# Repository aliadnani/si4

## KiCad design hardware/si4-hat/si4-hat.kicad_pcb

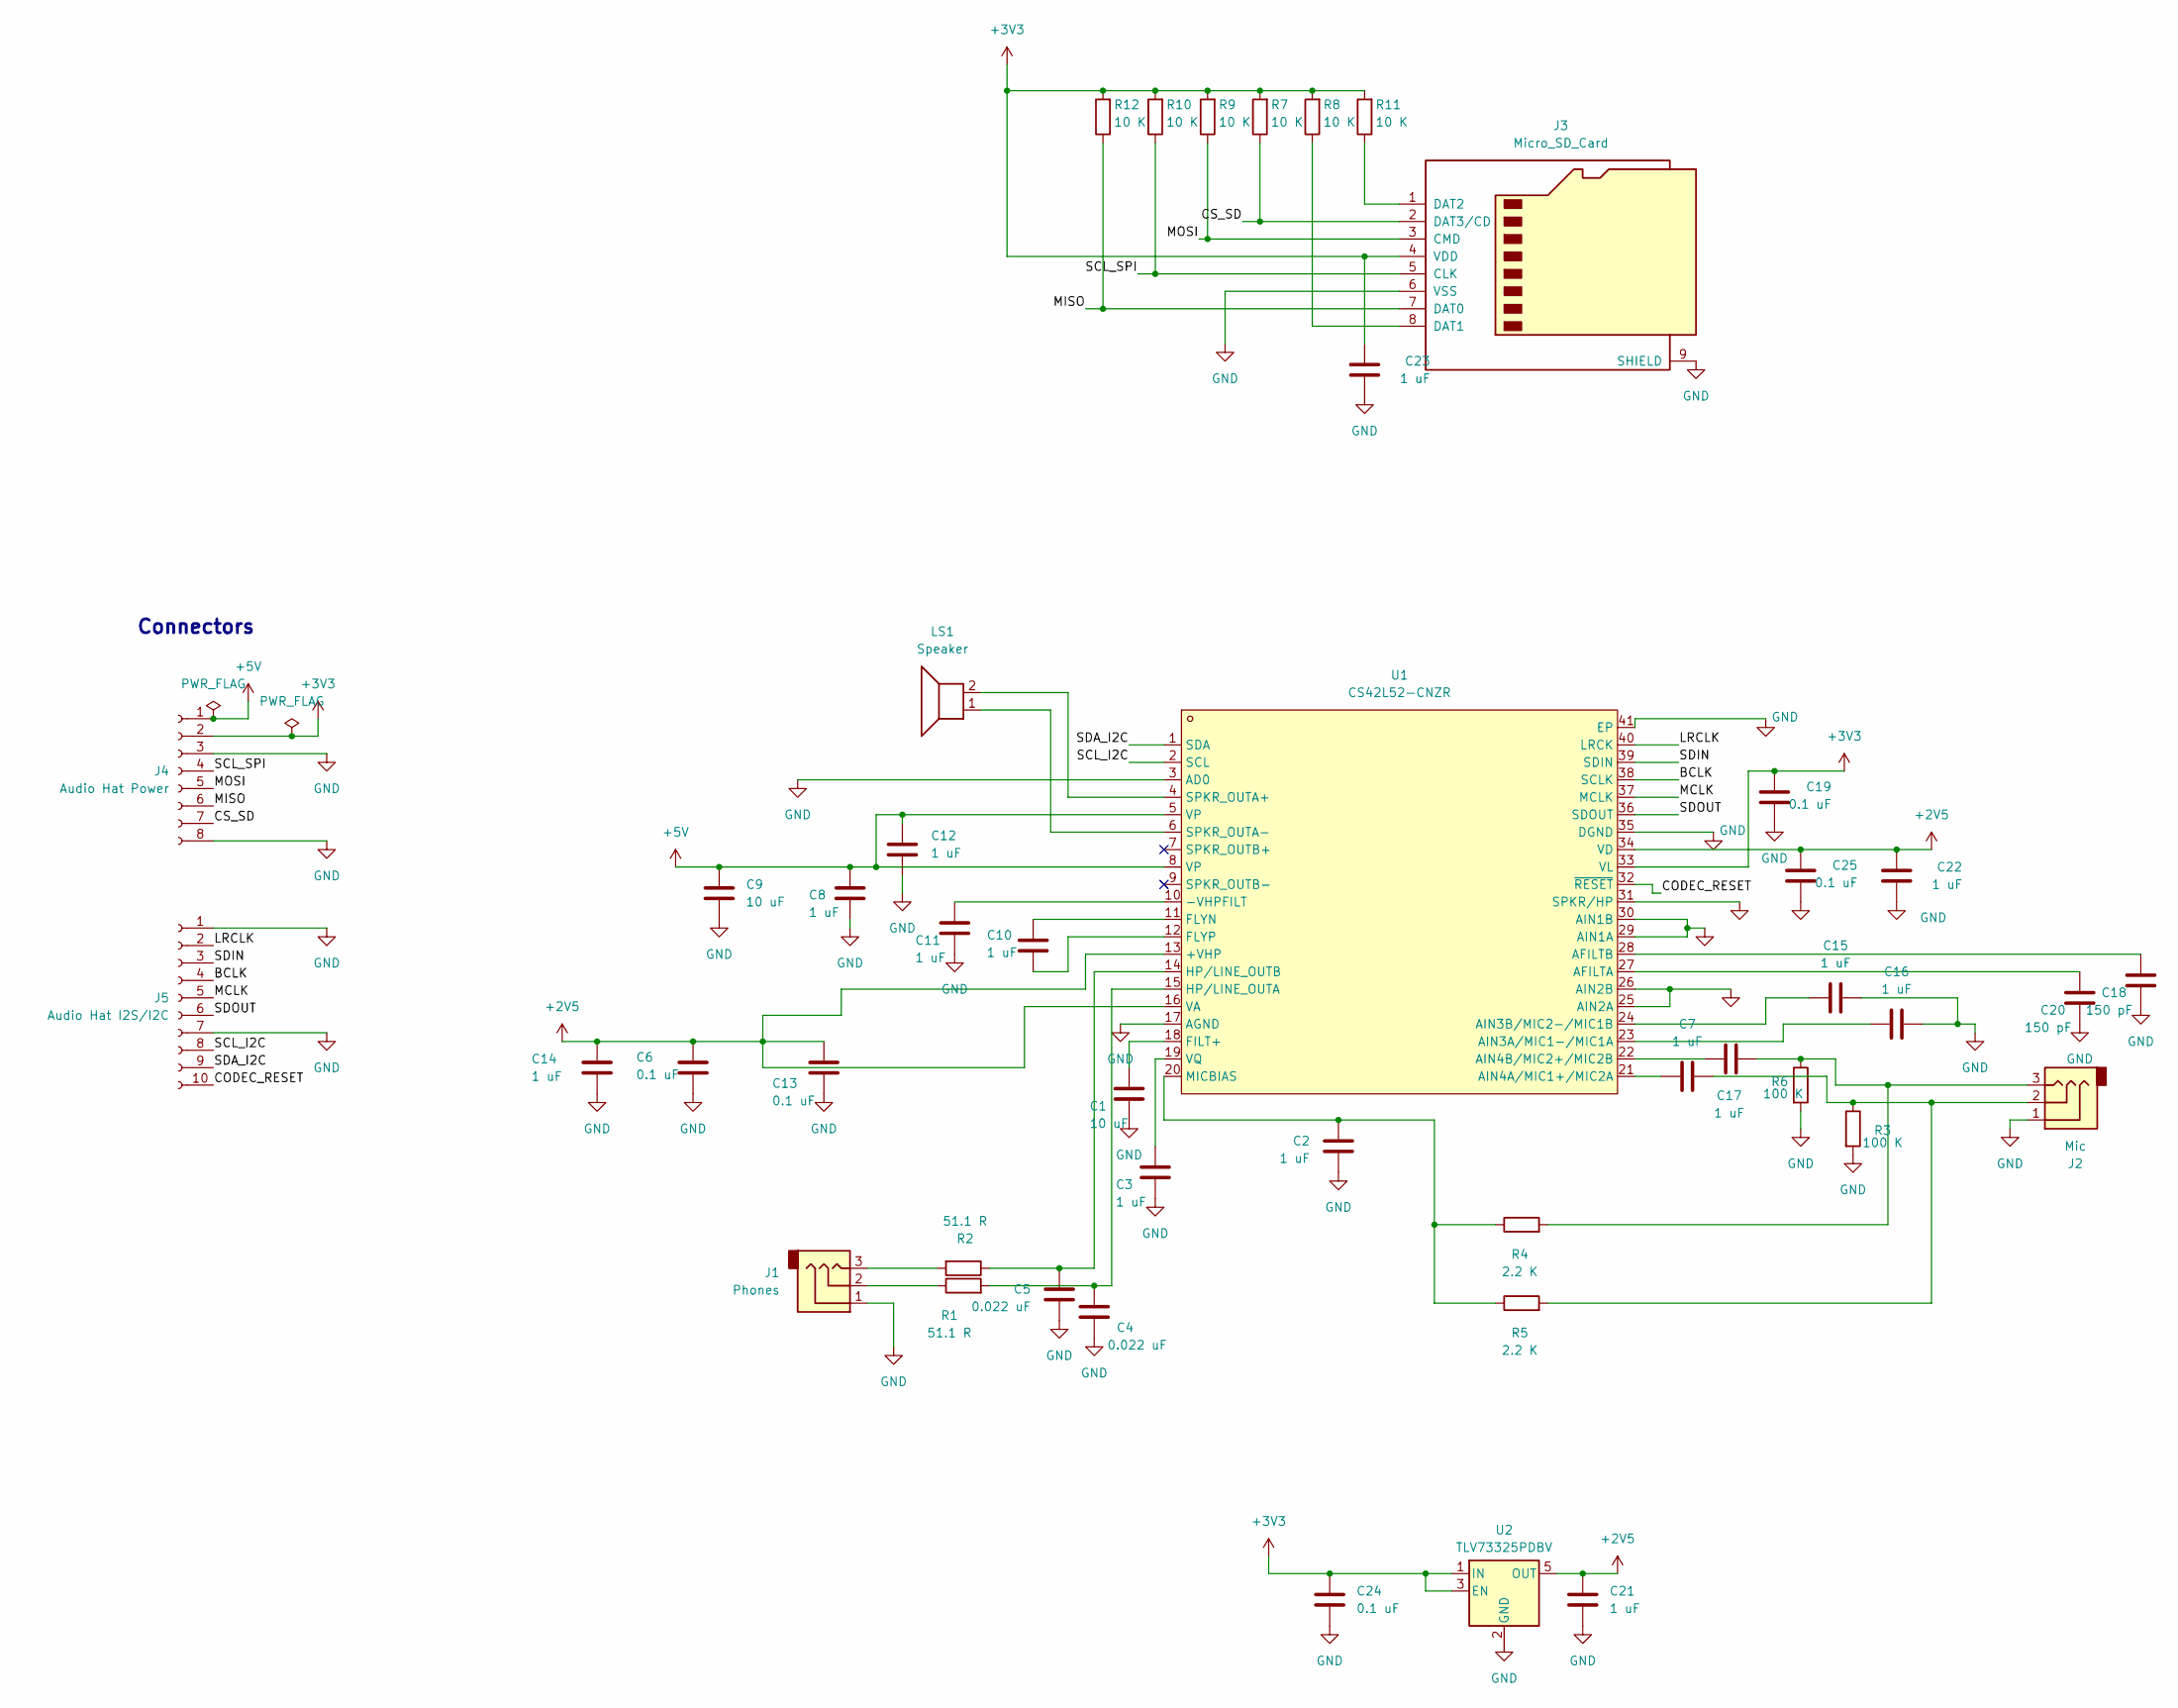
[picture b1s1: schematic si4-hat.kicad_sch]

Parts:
C1, C9: 10 uF; C_0805_2012Metric
C2, C3, C7, C8, C10, C11, C12, C14, C15, C16, C17, C21, C22, C23: 1 uF; C_0805_2012Metric
C4, C5: 0.022 uF; C_0805_2012Metric
C6, C13, C19, C24, C25: 0.1 uF; C_0805_2012Metric
C18, C20: 150 pF; C_0805_2012Metric
J1: Phones; AUDIO-TH_PJ-309A-2; JLC_3DModel_Q b7cd142673524e80947edf82ed32f13f
J2: Mic; AUDIO-TH_PJ-309A-2; JLC_3DModel_Q b7cd142673524e80947edf82ed32f13f
J3: Micro_SD_Card; microSD_HC_Hirose_DM3AT-SF-PEJM5
J4: Audio Hat Power; PinHeader_1x08_P1.27mm_Vertical
J5: Audio Hat I2S/I2C; PinHeader_1x10_P1.27mm_Vertical
LS1: Speaker; SolderWire-0.15sqmm_1x02_P4mm_D0.5mm_OD1.5mm
R1, R2: 51.1 R; R_0805_2012Metric
R3, R6: 100 K; R_0805_2012Metric
R4, R5: 2.2 K; R_0805_2012Metric
R7, R8, R9, R10, R11, R12: 10 K; R_0805_2012Metric
U1: CS42L52-CNZR; QFN-40_L6.0-W6.0-P0.50-TL-EP4.1; LCSC Part C17429034
U2: TLV73325PDBV; SOT-23-5

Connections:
+2V5: C6.1, C13.1, C14.1, C21.1, C22.1, C25.1, U1.13 (+VHP), U1.16 (VA), U1.34 (VD), U2.5 (OUT)
+3V3: C19.1, C23.1, C24.1, J3.4 (VDD), J4.2, R7.2, R8.2, R9.2, R10.2, R11.2, R12.2, U1.33 (VL), U2.1 (IN), U2.3 (EN)
+5V: C8.1, C9.1, C12.1, J4.1, U1.5 (VP), U1.8 (VP)
/BCLK: J5.4, U1.38 (SCLK)
/CODEC_RESET: J5.10, U1.32 (~RESET)
/CS_SD: J3.2 (DAT3/CD), J4.7, R7.1
/LRCLK: J5.2, U1.40 (LRCK)
/MCLK: J5.5, U1.37 (MCLK)
/MISO: J3.7 (DAT0), J4.6, R12.1
/MOSI: J3.3 (CMD), J4.5, R9.1
/SCL_I2C: J5.8, U1.2 (SCL)
/SCL_SPI: J3.5 (CLK), J4.4, R10.1
/SDA_I2C: J5.9, U1.1 (SDA)
/SDIN: J5.3, U1.39 (SDIN)
/SDOUT: J5.6, U1.36 (SDOUT)
GND: C1.2, C2.2, C3.2, C4.2, C5.2, C6.2, C8.2, C9.2, C11.2, C12.2, C13.2, C14.2, C15.1, C16.1, C18.2, C19.2, C20.2, C21.2, C22.2, C23.2, C24.2, C25.2, J1.1, J2.1, J3.6 (VSS), J3.9 (SHIELD), J4.3, J4.8, J5.1, J5.7, R3.2, R6.2, U1.3 (AD0), U1.17 (AGND), U1.25 (AIN2A), U1.26 (AIN2B), U1.29 (AIN1A), U1.30 (AIN1B), U1.31 (SPKR/HP), U1.35 (DGND), U1.41 (EP), U2.2 (GND)
unnamed: C7.1, J2.2, R3.1, R5.2
unnamed: C17.1, J2.3, R4.2, R6.1
unnamed: J1.2, R1.1
unnamed: J1.3, R2.2
unnamed: J3.8 (DAT1), R8.1
unnamed: J3.1 (DAT2), R11.1
unnamed: C11.1, U1.10 (-VHPFILT)
unnamed: C20.1, U1.27 (AFILTA)
unnamed: C18.1, U1.28 (AFILTB)
unnamed: C16.2, U1.23 (AIN3A/MIC1-/MIC1A)
unnamed: C15.2, U1.24 (AIN3B/MIC2-/MIC1B)
unnamed: C7.2, U1.21 (AIN4A/MIC1+/MIC2A)
unnamed: C17.2, U1.22 (AIN4B/MIC2+/MIC2B)
unnamed: C1.1, U1.18 (FILT+)
unnamed: C10.1, U1.11 (FLYN)
unnamed: C10.2, U1.12 (FLYP)
unnamed: C4.1, R1.2, U1.15 (HP/LINE_OUTA)
unnamed: C5.1, R2.1, U1.14 (HP/LINE_OUTB)
unnamed: C2.1, R4.1, R5.1, U1.20 (MICBIAS)
unnamed: LS1.2, U1.4 (SPKR_OUTA+)
unnamed: LS1.1, U1.6 (SPKR_OUTA-)
unnamed: C3.1, U1.19 (VQ)

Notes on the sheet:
Connectors

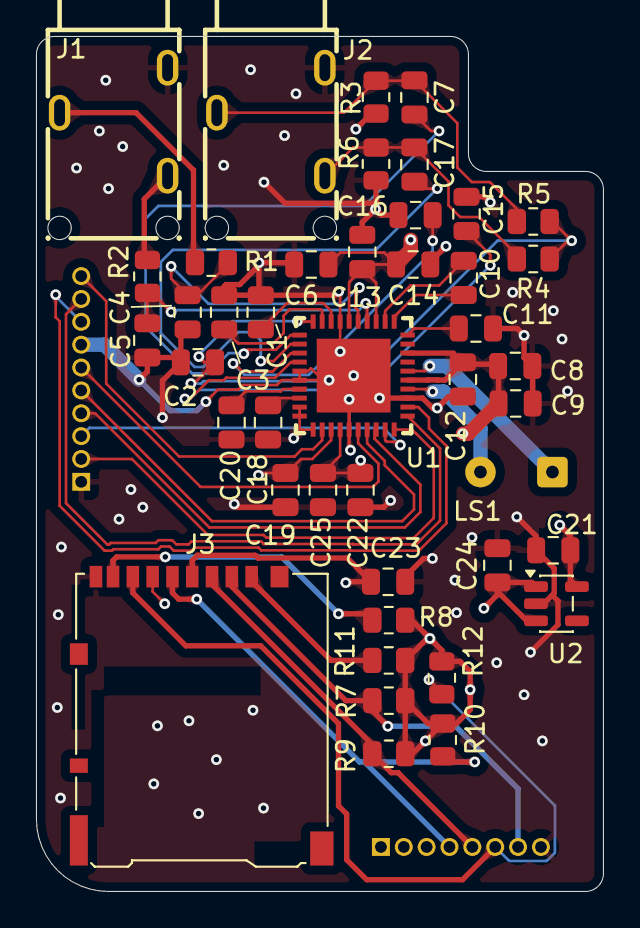
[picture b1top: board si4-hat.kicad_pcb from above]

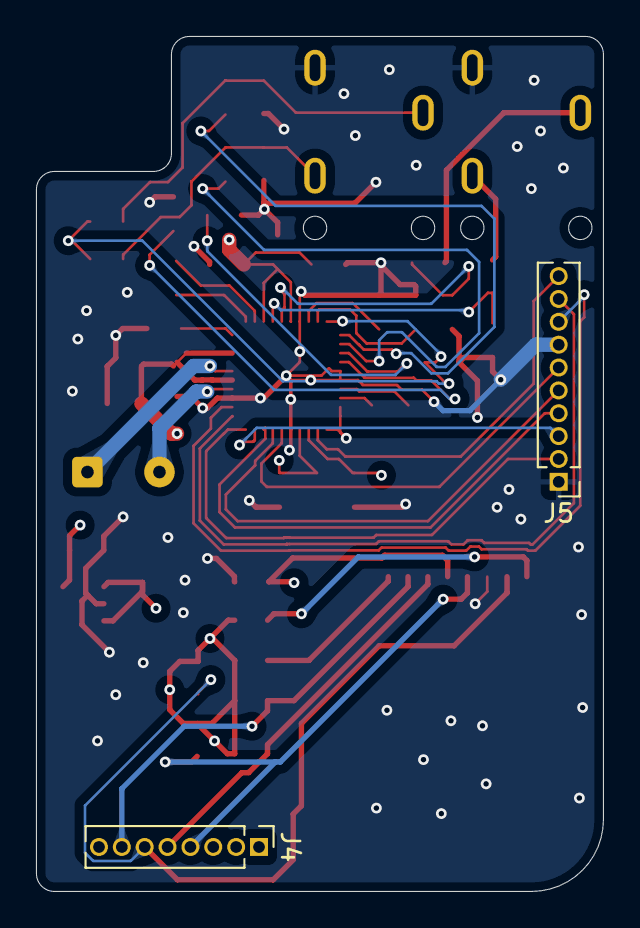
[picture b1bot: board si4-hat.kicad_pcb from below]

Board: 4 copper layers, 31.5 x 47.5 mm, 45 parts (2 on the bottom side), 38 nets.

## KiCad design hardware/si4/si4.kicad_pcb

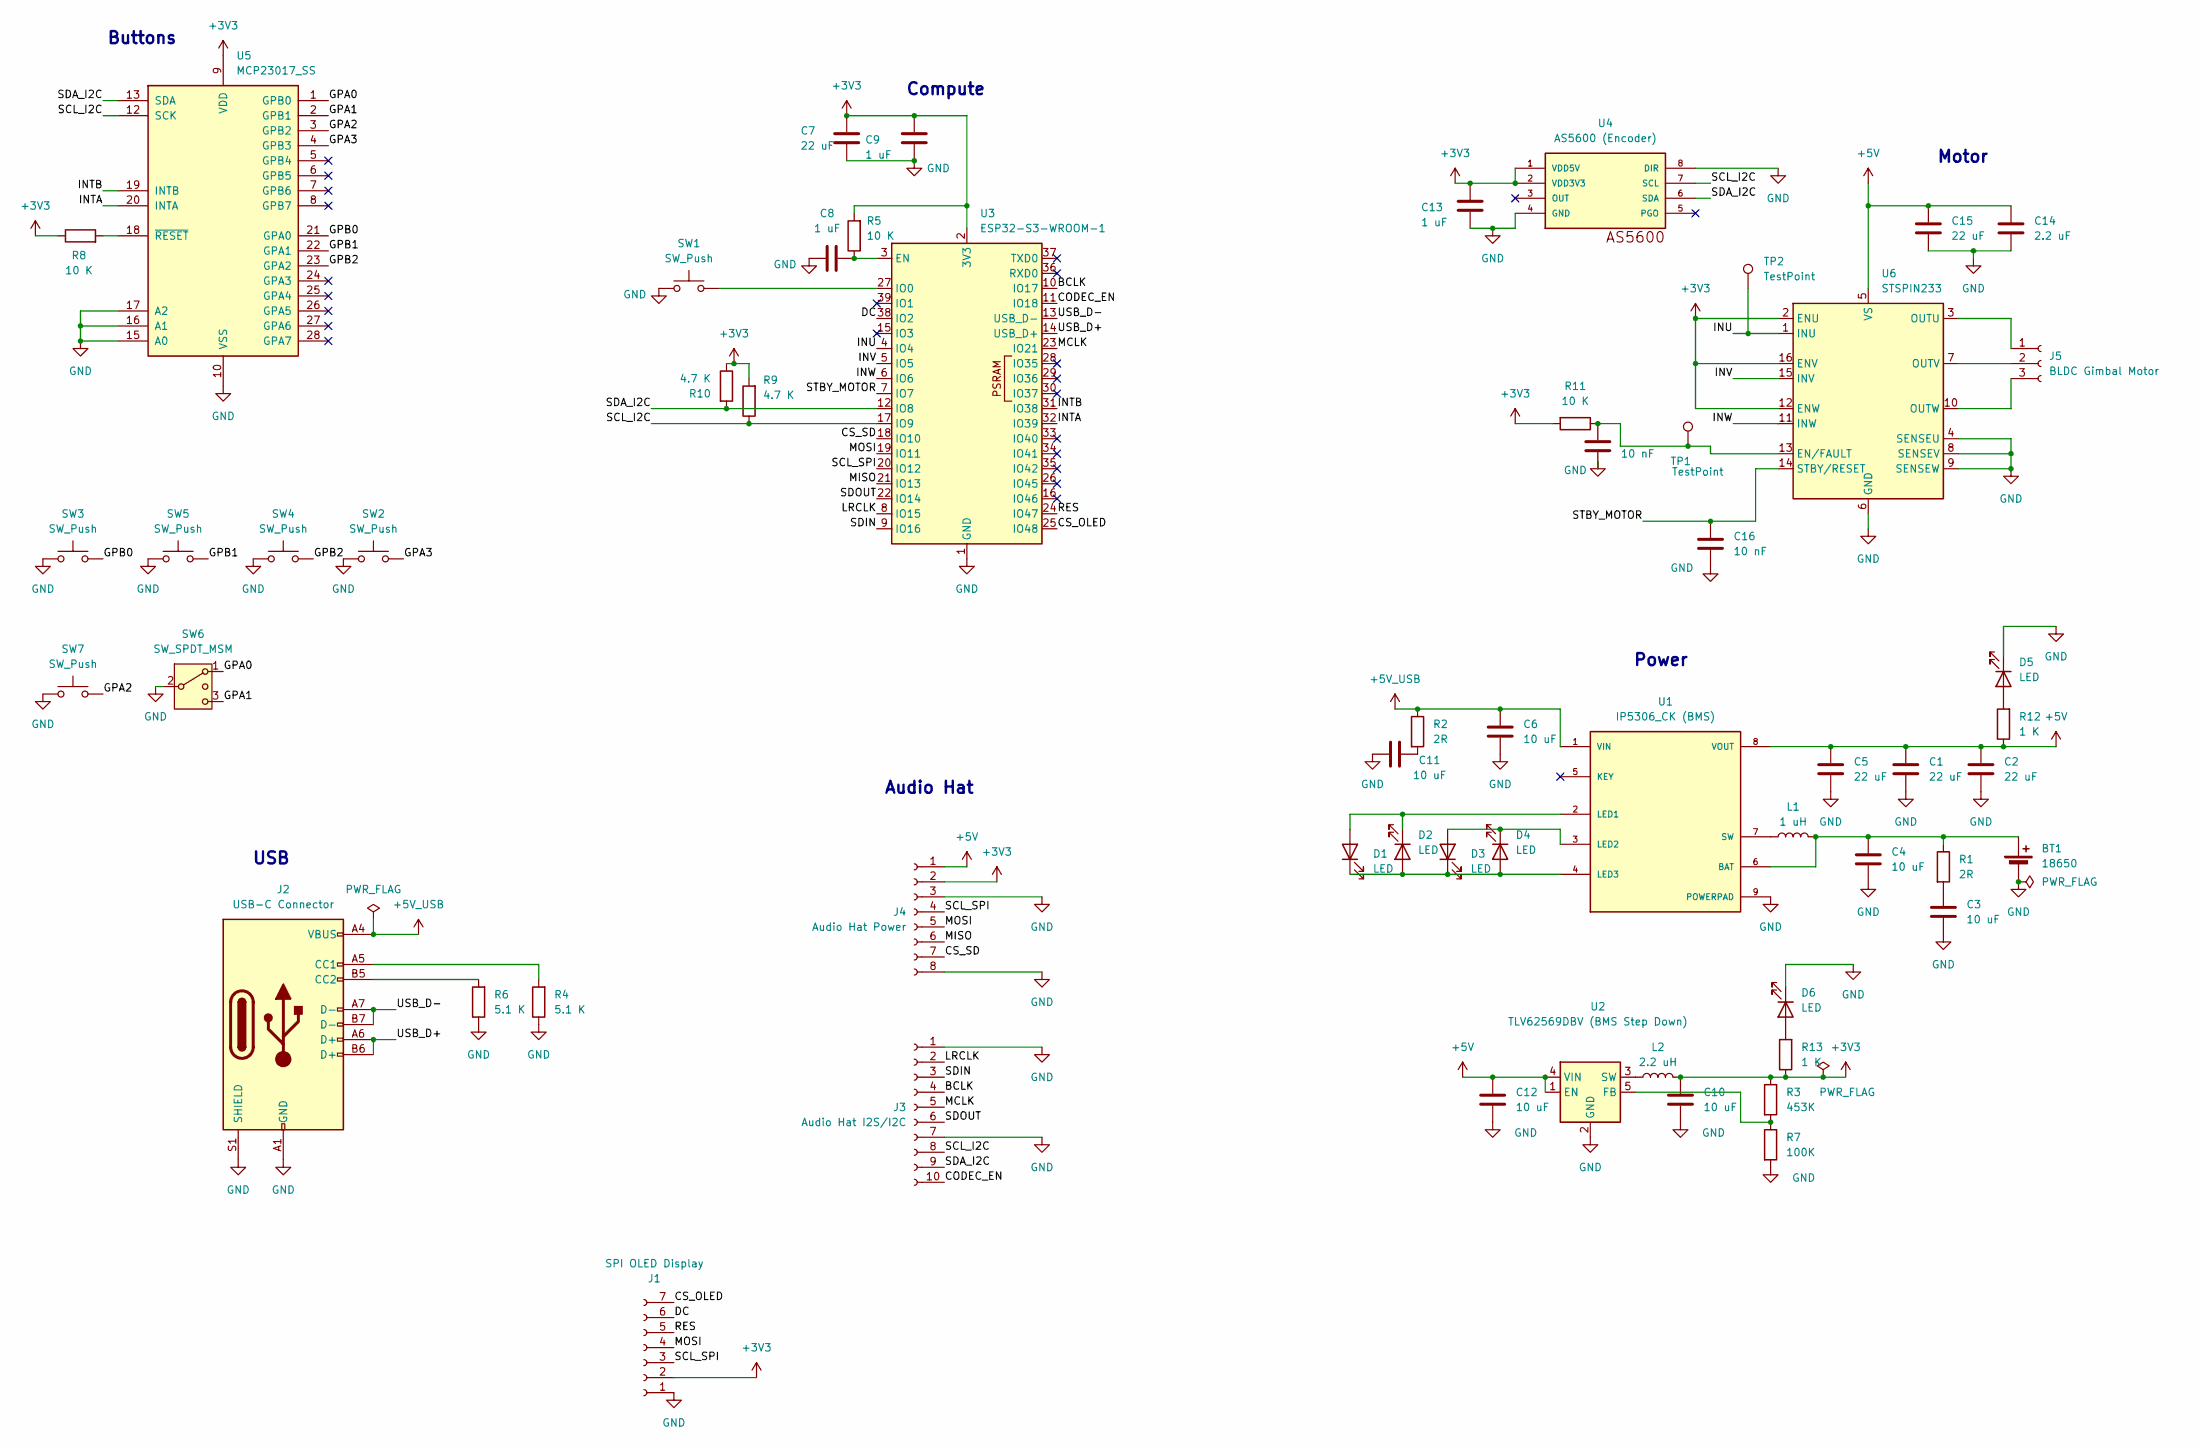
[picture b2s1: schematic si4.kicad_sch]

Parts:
BT1: 18650; SolderWire-0.75sqmm_1x02_P7mm_D1.25mm_OD3.5mm
C1, C2, C5, C7, C15: 22 uF; C_1206_3216Metric_Pad1.33x1.80mm_HandSolder
C3, C4, C6, C10, C11, C12: 10 uF; C_1206_3216Metric_Pad1.33x1.80mm_HandSolder
C8, C9, C13: 1 uF; C_0805_2012Metric_Pad1.18x1.45mm_HandSolder
C14: 2.2 uF; C_0805_2012Metric_Pad1.18x1.45mm_HandSolder
C16, C17: 10 nF; C_0805_2012Metric_Pad1.18x1.45mm_HandSolder
D1, D2, D3, D4, D5, D6: LED; LED_0805_2012Metric_Pad1.15x1.40mm_HandSolder
J1: SPI OLED Display; PinSocket_1x07_P2.54mm_Vertical
J2: USB-C Connector; USB_C_Receptacle_XKB_U262-16XN-4BVC11
J3: Audio Hat I2S/I2C; PinSocket_1x10_P1.27mm_Vertical
J4: Audio Hat Power; PinSocket_1x08_P1.27mm_Vertical
J5: BLDC Gimbal Motor; SolderWire-0.75sqmm_1x03_P7mm_D1.25mm_OD3.5mm
L1: 1 uH; L_Taiyo-Yuden_NR-40xx_HandSoldering
L2: 2.2 uH; L_Taiyo-Yuden_NR-40xx_HandSoldering
R1, R2: 2R; R_0805_2012Metric_Pad1.20x1.40mm_HandSolder
R3: 453K; R_0805_2012Metric_Pad1.20x1.40mm_HandSolder
R4, R6: 5.1 K; R_0805_2012Metric_Pad1.20x1.40mm_HandSolder
R5, R8, R11: 10 K; R_0805_2012Metric_Pad1.20x1.40mm_HandSolder
R7: 100K; R_0805_2012Metric_Pad1.20x1.40mm_HandSolder
R9, R10: 4.7 K; R_0805_2012Metric_Pad1.20x1.40mm_HandSolder
R12, R13: 1 K; R_0805_2012Metric_Pad1.20x1.40mm_HandSolder
SW1: SW_Push; SW_SPST_TS-1088-xR020
SW2, SW3, SW4, SW5, SW7: SW_Push; SW_Hotswap_Kailh_MX
SW6: SW_SPDT_MSM; MTS-103 Switch
TP1, TP2: TestPoint; TestPoint_Pad_1.0x1.0mm
U1: IP5306_CK (BMS); SOIC-8-1EP_3.9x4.9mm_P1.27mm_EP2.29x3mm; PARTREV 1.31
U2: TLV62569DBV (BMS Step Down); SOT-23-5
U3: ESP32-S3-WROOM-1
U4: AS5600 (Encoder); SOIC-8_3.9x4.9mm_P1.27mm
U5: MCP23017_SS; SSOP-28_5.3x10.2mm_P0.65mm
U6: STSPIN233; VQFN-16-1EP_3x3mm_P0.5mm_EP1.8x1.8mm

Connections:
+3V3: C7.1, C9.1, C10.1, C13.1, J1.2, J4.2, L2.2, R3.1, R5.2, R8.1, R9.2, R10.1, R11.2, R13.1, U3.2 (3V3), U4.1 (VDD5V), U4.2 (VDD3V3), U5.9 (VDD), U6.2 (ENU), U6.12 (ENW), U6.16 (ENV)
+5V: C1.1, C2.1, C5.1, C12.1, C14.1, C15.1, J4.1, R12.1, U1.8 (VOUT), U2.1 (EN), U2.4 (VIN), U6.5 (VS)
+5V_USB: C6.1, J2.A4 (VBUS), J2.A9 (VBUS), J2.B4 (VBUS), J2.B9 (VBUS), R2.1, U1.1 (VIN)
/BCLK: J3.4, U3.10 (IO17)
/CODEC_EN: J3.10, U3.11 (IO18)
/CS_OLED: J1.7, U3.25 (IO48)
/CS_SD: J4.7, U3.18 (IO10)
/DC: J1.6, U3.38 (IO2)
/GPA0: SW6.1, U5.1 (GPB0)
/GPA1: SW6.3 (4), U5.2 (GPB1)
/GPA2: SW7.2, U5.3 (GPB2)
/GPA3: SW2.2, U5.4 (GPB3)
/GPB0: SW3.2, U5.21 (GPA0)
/GPB1: SW5.2, U5.22 (GPA1)
/GPB2: SW4.2, U5.23 (GPA2)
/INTA: U3.32 (IO39), U5.20 (INTA)
/INTB: U3.31 (IO38), U5.19 (INTB)
/INU: TP2.1, U3.4 (IO4), U6.1 (INU)
/INV: U3.5 (IO5), U6.15 (INV)
/INW: U3.6 (IO6), U6.11 (INW)
/LRCLK: J3.2, U3.8 (IO15)
/MCLK: J3.5, U3.23 (IO21)
/MISO: J4.6, U3.21 (IO13)
/MOSI: J1.4, J4.5, U3.19 (IO11)
/RES: J1.5, U3.24 (IO47)
/SCL_I2C: J3.8, R9.1, U3.17 (IO9), U4.7 (SCL), U5.12 (SCK)
/SCL_SPI: J1.3, J4.4, U3.20 (IO12)
/SDA_I2C: J3.9, R10.2, U3.12 (IO8), U4.6 (SDA), U5.13 (SDA)
/SDIN: J3.3, U3.9 (IO16)
/SDOUT: J3.6, U3.22 (IO14)
/STBY_MOTOR: C16.1, U3.7 (IO7), U6.14 (STBY/RESET)
/USB_D+: J2.A6 (D+), J2.B6 (D+), U3.14 (USB_D+)
/USB_D-: J2.A7 (D-), J2.B7 (D-), U3.13 (USB_D-)
GND: BT1.2 (-), C1.2, C2.2, C3.2, C4.2, C5.2, C6.2, C7.2, C8.2, C9.2, C10.2, C11.1, C12.2, C13.2, C14.2, C15.2, C16.2, C17.2, D5.1 (K), D6.1 (K), J1.1, J2.A1 (GND), J2.A12 (GND), J2.B1 (GND), J2.B12 (GND), J2.S1 (SHIELD), J3.1, J3.7, J4.3, J4.8, R4.1, R6.1, R7.2, SW1.1, SW2.1, SW3.1, SW4.1, SW5.1, SW6.2 (3), SW7.1, U1.9 (POWERPAD), U2.2 (GND), U3.1 (GND), U3.40 (GND), U3.41 (GND), U4.4 (GND), U4.8 (DIR), U5.10 (VSS), U5.15 (A0), U5.16 (A1), U5.17 (A2), U6.4 (SENSEU), U6.6 (GND), U6.8 (SENSEV), U6.9 (SENSEW), U6.17 (GND)
unnamed: BT1.1 (+), C4.1, L1.2, R1.1, U1.6 (BAT)
unnamed: C3.1, R1.2
unnamed: C11.2, R2.2
unnamed: D1.2 (A), D2.1 (K), U1.2 (LED1)
unnamed: D1.1 (K), D2.2 (A), D3.1 (K), D4.2 (A), U1.4 (LED3)
unnamed: D3.2 (A), D4.1 (K), U1.3 (LED2)
unnamed: D5.2 (A), R12.2
unnamed: D6.2 (A), R13.2
unnamed: J2.A5 (CC1), R4.2
unnamed: J2.B5 (CC2), R6.2
unnamed: J5.1, U6.3 (OUTU)
unnamed: J5.2, U6.7 (OUTV)
unnamed: J5.3, U6.10 (OUTW)
unnamed: L1.1, U1.7 (SW)
unnamed: R3.2, R7.1, U2.5 (FB)
unnamed: L2.1, U2.3 (SW)
unnamed: C8.1, R5.1, U3.3 (EN)
unnamed: SW1.2, U3.27 (IO0)
unnamed: R8.2, U5.18 (~RESET)
unnamed: C17.1, R11.1, TP1.1, U6.13 (EN/FAULT)

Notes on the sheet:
Buttons
Power
Audio Hat
USB
Motor
Compute

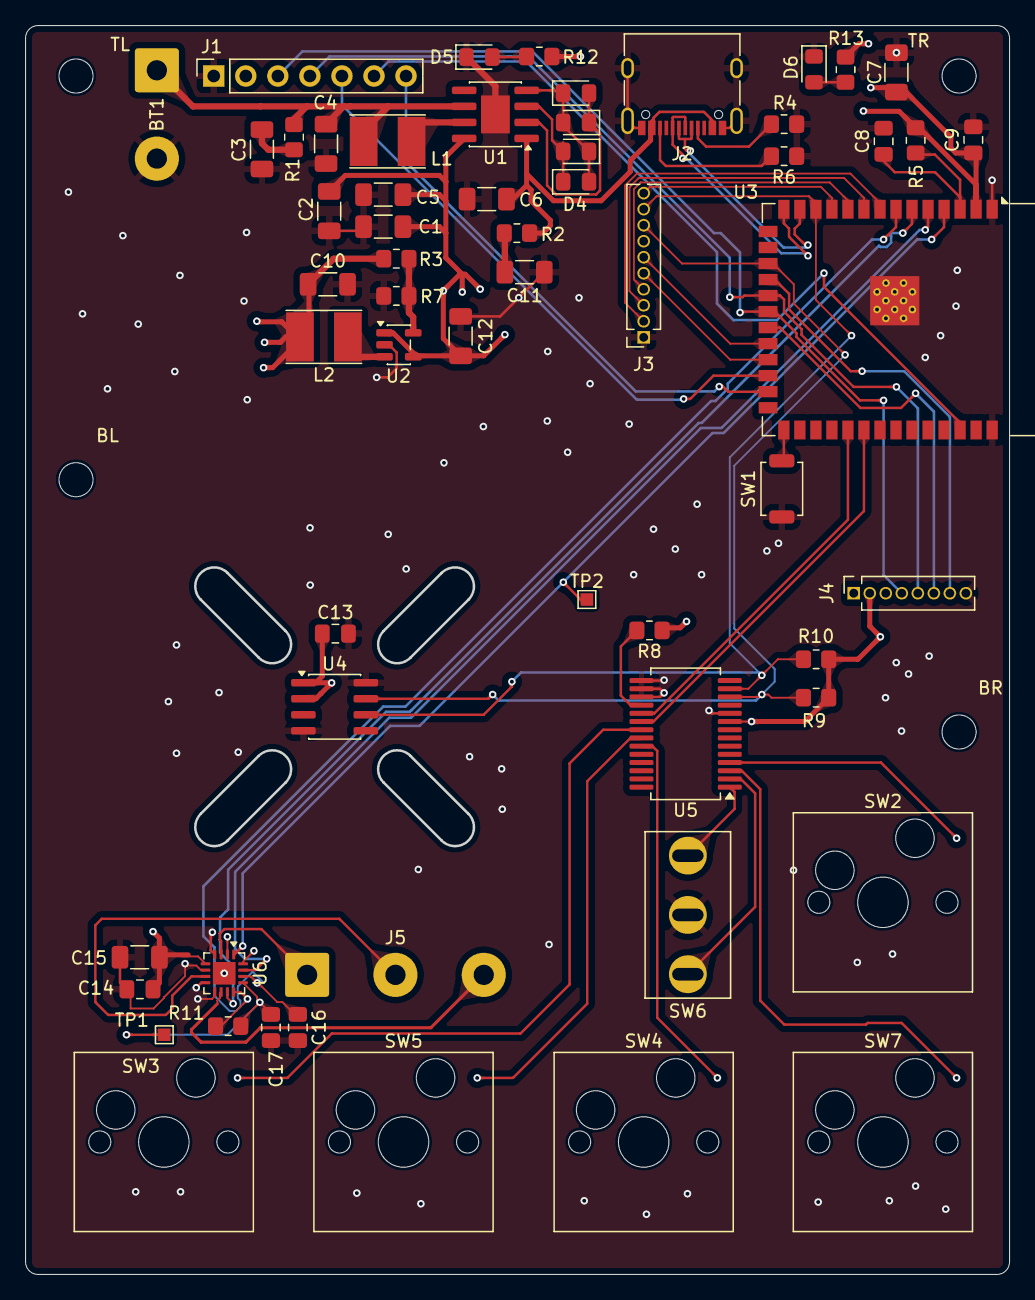
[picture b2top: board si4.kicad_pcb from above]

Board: 4 copper layers, 77.9 x 98.9 mm, 63 parts (0 on the bottom side), 54 nets.

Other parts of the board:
BL: MountingHole_2.7mm_M2.5
BR: MountingHole_2.7mm_M2.5
TL: MountingHole_2.7mm_M2.5
TR: MountingHole_2.7mm_M2.5

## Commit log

2026-04-03 init: hardware design
2026-04-05 init: firmware
2026-04-05 feat: compiles but doesn't run
2026-04-05 feat: log button press
